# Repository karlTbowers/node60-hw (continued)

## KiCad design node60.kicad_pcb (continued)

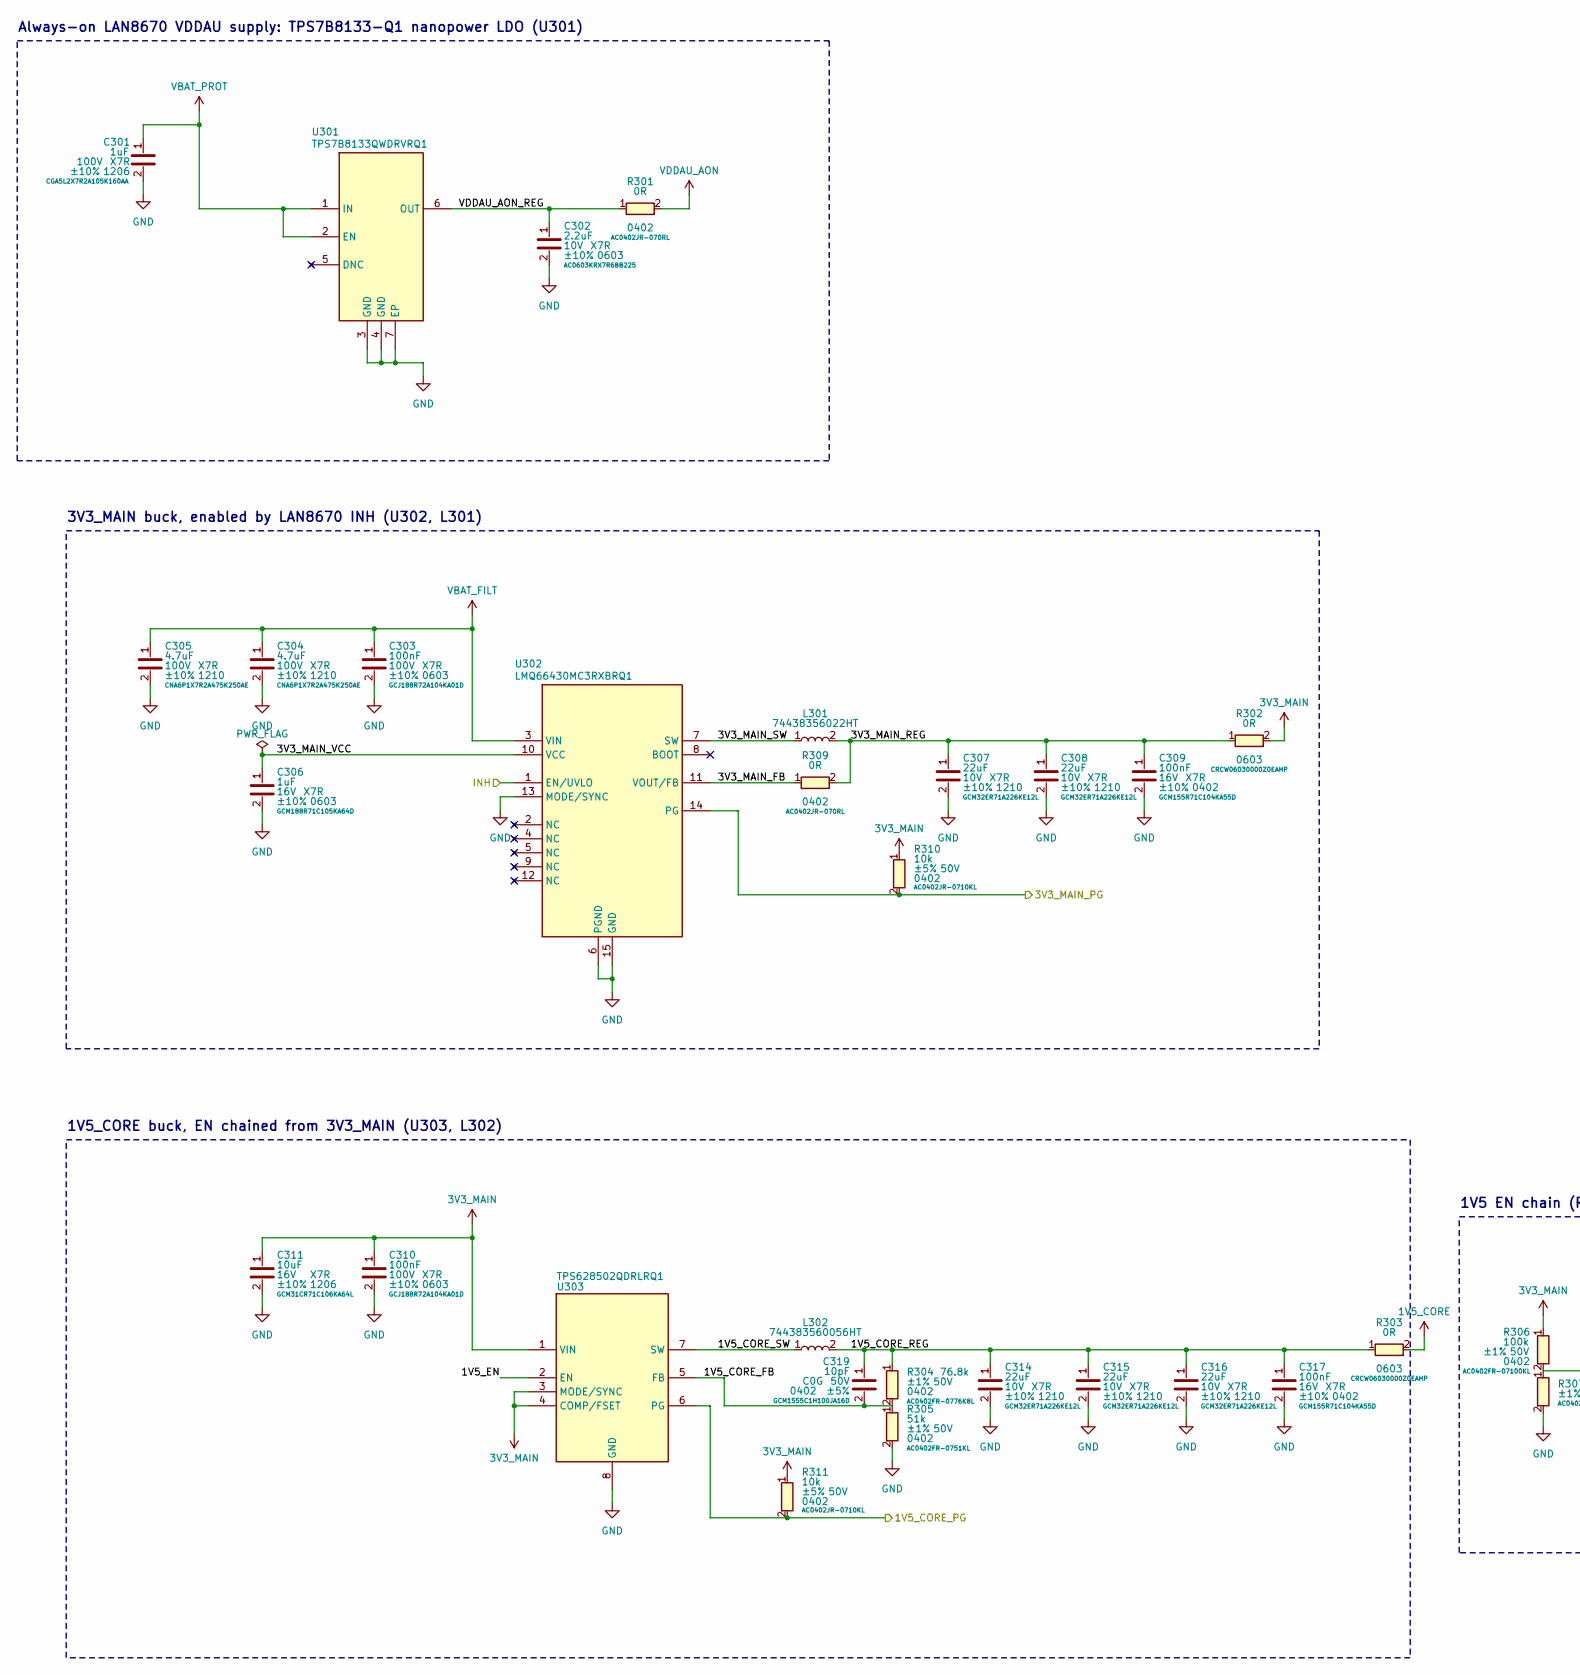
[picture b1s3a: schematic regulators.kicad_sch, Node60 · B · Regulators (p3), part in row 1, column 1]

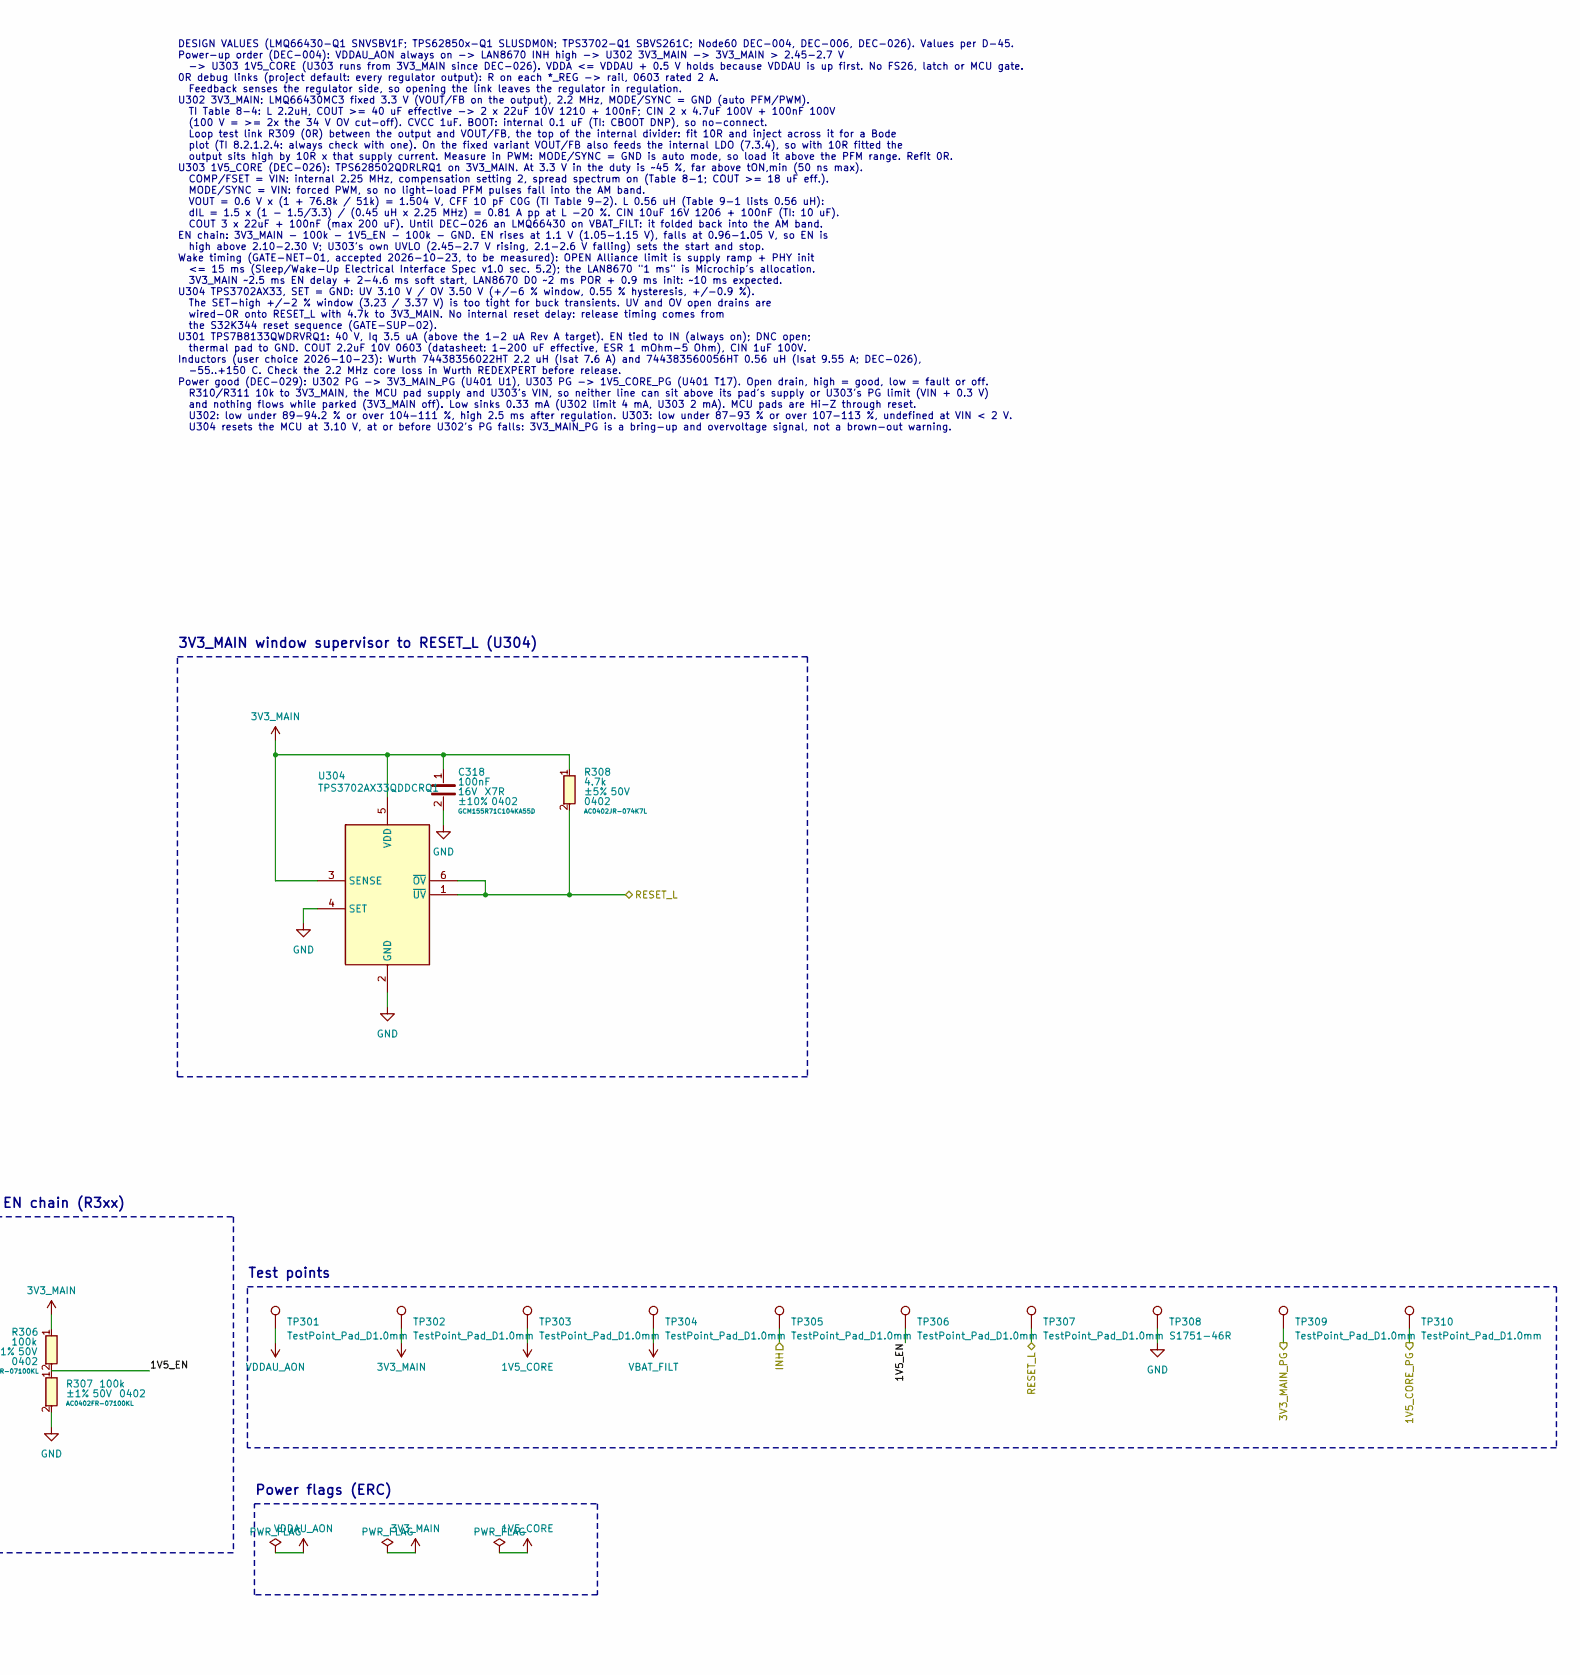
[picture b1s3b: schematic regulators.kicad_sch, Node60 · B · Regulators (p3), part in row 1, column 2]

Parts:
C301: 1uF; C_1206_3216Metric; Voltage 100V; Tolerance ±10%; MPN CGA5L2X7R2A105K160AA; DigiKey_PN 445-5845-1-ND
C302: 2.2uF; C_0603_1608Metric; Voltage 10V; Tolerance ±10%; MPN AC0603KRX7R6BB225; DigiKey_PN 13-AC0603KRX7R6BB225CT-ND
C303, C310: 100nF; C_0603_1608Metric; Voltage 100V; Tolerance ±10%; MPN GCJ188R72A104KA01D; DigiKey_PN 490-13420-1-ND
C304, C305: 4.7uF; C_1210_3225Metric; Voltage 100V; Tolerance ±10%; MPN CNA6P1X7R2A475K250AE; DigiKey_PN 445-181409-1-ND
C306: 1uF; C_0603_1608Metric; Voltage 16V; Tolerance ±10%; MPN GCM188R71C105KA64D; DigiKey_PN 490-5241-1-ND
C307, C308, C314, C315, C316: 22uF; C_1210_3225Metric; Voltage 10V; Tolerance ±10%; MPN GCM32ER71A226KE12L; DigiKey_PN 490-4797-1-ND
C309, C317, C318: 100nF; C_0402_1005Metric; Voltage 16V; Tolerance ±10%; MPN GCM155R71C104KA55D; DigiKey_PN 490-4759-1-ND
C311: 10uF; C_1206_3216Metric; Voltage 16V; Tolerance ±10%; MPN GCM31CR71C106KA64L; DigiKey_PN 490-4793-1-ND
C319: 10pF; C_0402_1005Metric; Voltage 50V; Tolerance ±5%; MPN GCM1555C1H100JA16D; DigiKey_PN 490-10668-1-ND
L301: 74438356022HT; L_Wuerth_MAPI-4020; MPN 74438356022HT; DigiKey_PN 732-74438356022HTCT-ND
L302: 744383560056HT; L_Wuerth_MAPI-4020; MPN 744383560056HT; DigiKey_PN 732-744383560056HTCT-ND
R301, R309: 0R; R_0402_1005Metric; MPN AC0402JR-070RL; DigiKey_PN 311-0.0LBCT-ND
R302, R303: 0R; R_0603_1608Metric; MPN CRCW06030000Z0EAHP; DigiKey_PN 541-0.0SBCT-ND
R304: 76.8k; R_0402_1005Metric; Tolerance ±1%; Voltage 50V; MPN AC0402FR-0776K8L; DigiKey_PN 13-AC0402FR-0776K8LCT-ND
R305: 51k; R_0402_1005Metric; Tolerance ±1%; Voltage 50V; MPN AC0402FR-0751KL; DigiKey_PN YAG3499CT-ND
R306, R307: 100k; R_0402_1005Metric; Tolerance ±1%; Voltage 50V; MPN AC0402FR-07100KL; DigiKey_PN YAG3434CT-ND
R308: 4.7k; R_0402_1005Metric; Tolerance ±5%; Voltage 50V; MPN AC0402JR-074K7L; DigiKey_PN 311-4.7KLBCT-ND
R310, R311: 10k; R_0402_1005Metric; Tolerance ±5%; Voltage 50V; MPN AC0402JR-0710KL; DigiKey_PN YAG3517CT-ND
TP301, TP302, TP303, TP304, TP305, TP306, TP307, TP309, TP310: TestPoint_Pad_D1.0mm; MPN TestPoint_Pad_D1.0mm
TP308: S1751-46R; TestPoint_Harwin_S1751; MPN S1751-46R; DigiKey_PN 952-1478-1-ND
U301: TPS7B8133QWDRVRQ1; Texas_DRV0006A_WSON-6-1EP_2x2mm_P0.65mm_EP1x1.6mm; MPN TPS7B8133QWDRVRQ1; DigiKey_PN 296-TPS7B8133QWDRVRQ1CT-ND
U302: LMQ66430MC3RXBRQ1; Texas_RXB0014A_VQFN-14-1EP_2.6x2.6mm_P0.5mm_EP1x1mm; MPN LMQ66430MC3RXBRQ1; DigiKey_PN 296-LMQ66430MC3RXBRQ1CT-ND
U303: TPS628502QDRLRQ1; Texas_DRL0008A_SOT-583-8; MPN TPS628502QDRLRQ1; DigiKey_PN 296-TPS628502QDRLRQ1CT-ND
U304: TPS3702AX33QDDCRQ1; Texas_DDC0006A_TSOT-23-6; MPN TPS3702AX33QDDCRQ1; DigiKey_PN 296-51914-2-ND

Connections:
1V5_CORE: R303.2, TP303.1 (1_1); also elsewhere on the board
3V3_MAIN: C310.1, C311.1, C318.1, R302.2, R306.1, R308.1, R310.1, R311.1, TP302.1 (1_1), U303.1 (VIN), U303.3 (MODE/SYNC), U303.4 (COMP/FSET), U304.3 (SENSE), U304.5 (VDD); also elsewhere on the board
/1V5_CORE_PG: R311.2, TP310.1 (1_1), U303.6 (PG); also elsewhere on the board
/3V3_MAIN_PG: R310.2, TP309.1 (1_1), U302.14 (PG); also elsewhere on the board
/INH: TP305.1 (1_1), U302.1 (EN/UVLO); also elsewhere on the board
/RESET_L: R308.2, TP307.1 (1_1), U304.1 (~UV), U304.6 (~OV); also elsewhere on the board
/Regulators/1V5_CORE_FB: C319.2, R304.2, R305.1, U303.5 (FB)
/Regulators/1V5_CORE_REG: C314.1, C315.1, C316.1, C317.1, C319.1, L302.2, R303.1, R304.1
/Regulators/1V5_CORE_SW: L302.1, U303.7 (SW)
/Regulators/1V5_EN: R306.2, R307.1, TP306.1 (1_1), U303.2 (EN)
/Regulators/3V3_MAIN_FB: R309.1, U302.11 (VOUT/FB)
/Regulators/3V3_MAIN_REG: C307.1, C308.1, C309.1, L301.2, R302.1, R309.2
/Regulators/3V3_MAIN_SW: L301.1, U302.7 (SW)
/Regulators/3V3_MAIN_VCC: C306.1, U302.10 (VCC)
/Regulators/VDDAU_AON_REG: C302.1, R301.1, U301.6 (OUT)
GND: C301.2, C302.2, C303.2, C304.2, C305.2, C306.2, C307.2, C308.2, C309.2, C310.2, C311.2, C314.2, C315.2, C316.2, C317.2, C318.2, R305.2, R307.2, TP308.1 (1_1), U301.3 (GND), U301.4 (GND), U301.7 (EP), U302.6 (PGND), U302.13 (MODE/SYNC), U302.15 (GND), U303.8 (GND), U304.2 (GND), U304.4 (SET); also elsewhere on the board
VBAT_FILT: C303.1, C304.1, C305.1, TP304.1 (1_1), U302.3 (VIN); also elsewhere on the board
VBAT_PROT: C301.1, U301.1 (IN), U301.2 (EN); also elsewhere on the board
VDDAU_AON: R301.2, TP301.1 (1_1); also elsewhere on the board

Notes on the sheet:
Always-on LAN8670 VDDAU supply: TPS7B8133-Q1 nanopower LDO (U301)
DESIGN VALUES (LMQ66430-Q1 SNVSBV1F; TPS62850x-Q1 SLUSDM0N; TPS3702-Q1 SBVS261C; Node60 DEC-004, DEC-006, DEC-026). Values per D-45. Power-up order (DEC-004): VDDAU_AON always on -> LAN8670 INH high -> U302 3V3_MAIN -> 3V3_MAIN > 2.45-2.7 V -> U303 1V5_CORE (U303 runs from 3V3_MAIN since DEC-026). 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
1V5_CORE buck, EN chained from 3V3_MAIN (U303, L302)
3V3_MAIN buck, enabled by LAN8670 INH (U302, L301)
Power flags (ERC)
Test points
1V5 EN chain (R3xx)
3V3_MAIN window supervisor to RESET_L (U304)

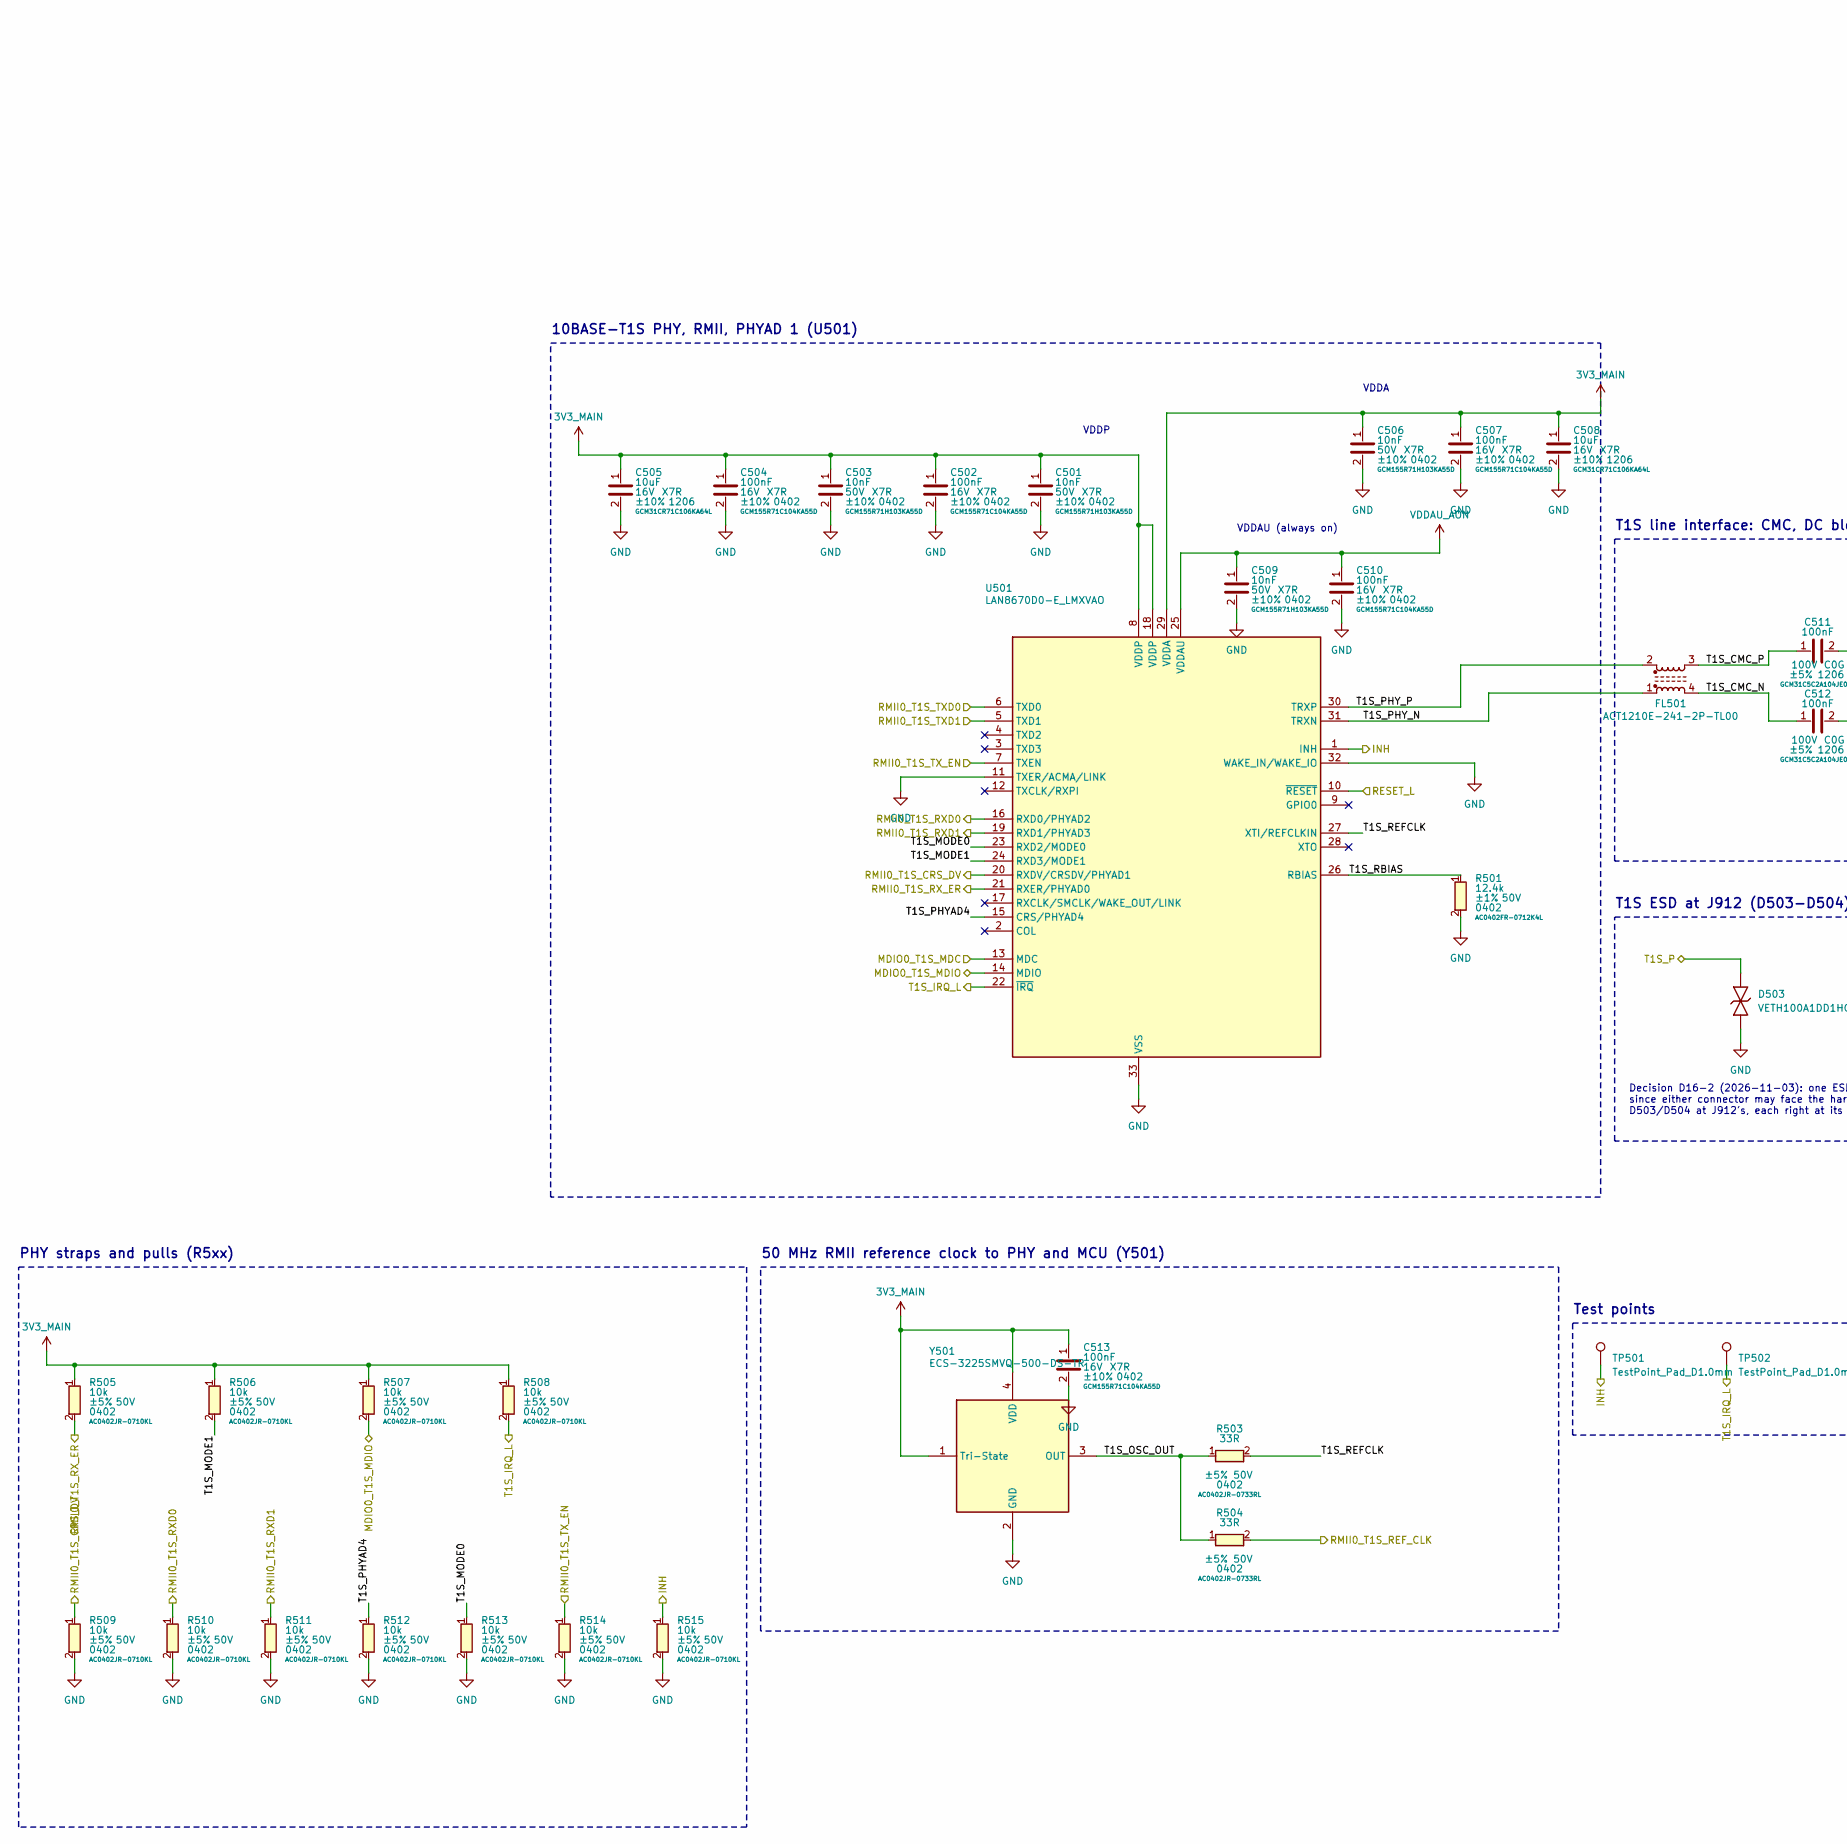
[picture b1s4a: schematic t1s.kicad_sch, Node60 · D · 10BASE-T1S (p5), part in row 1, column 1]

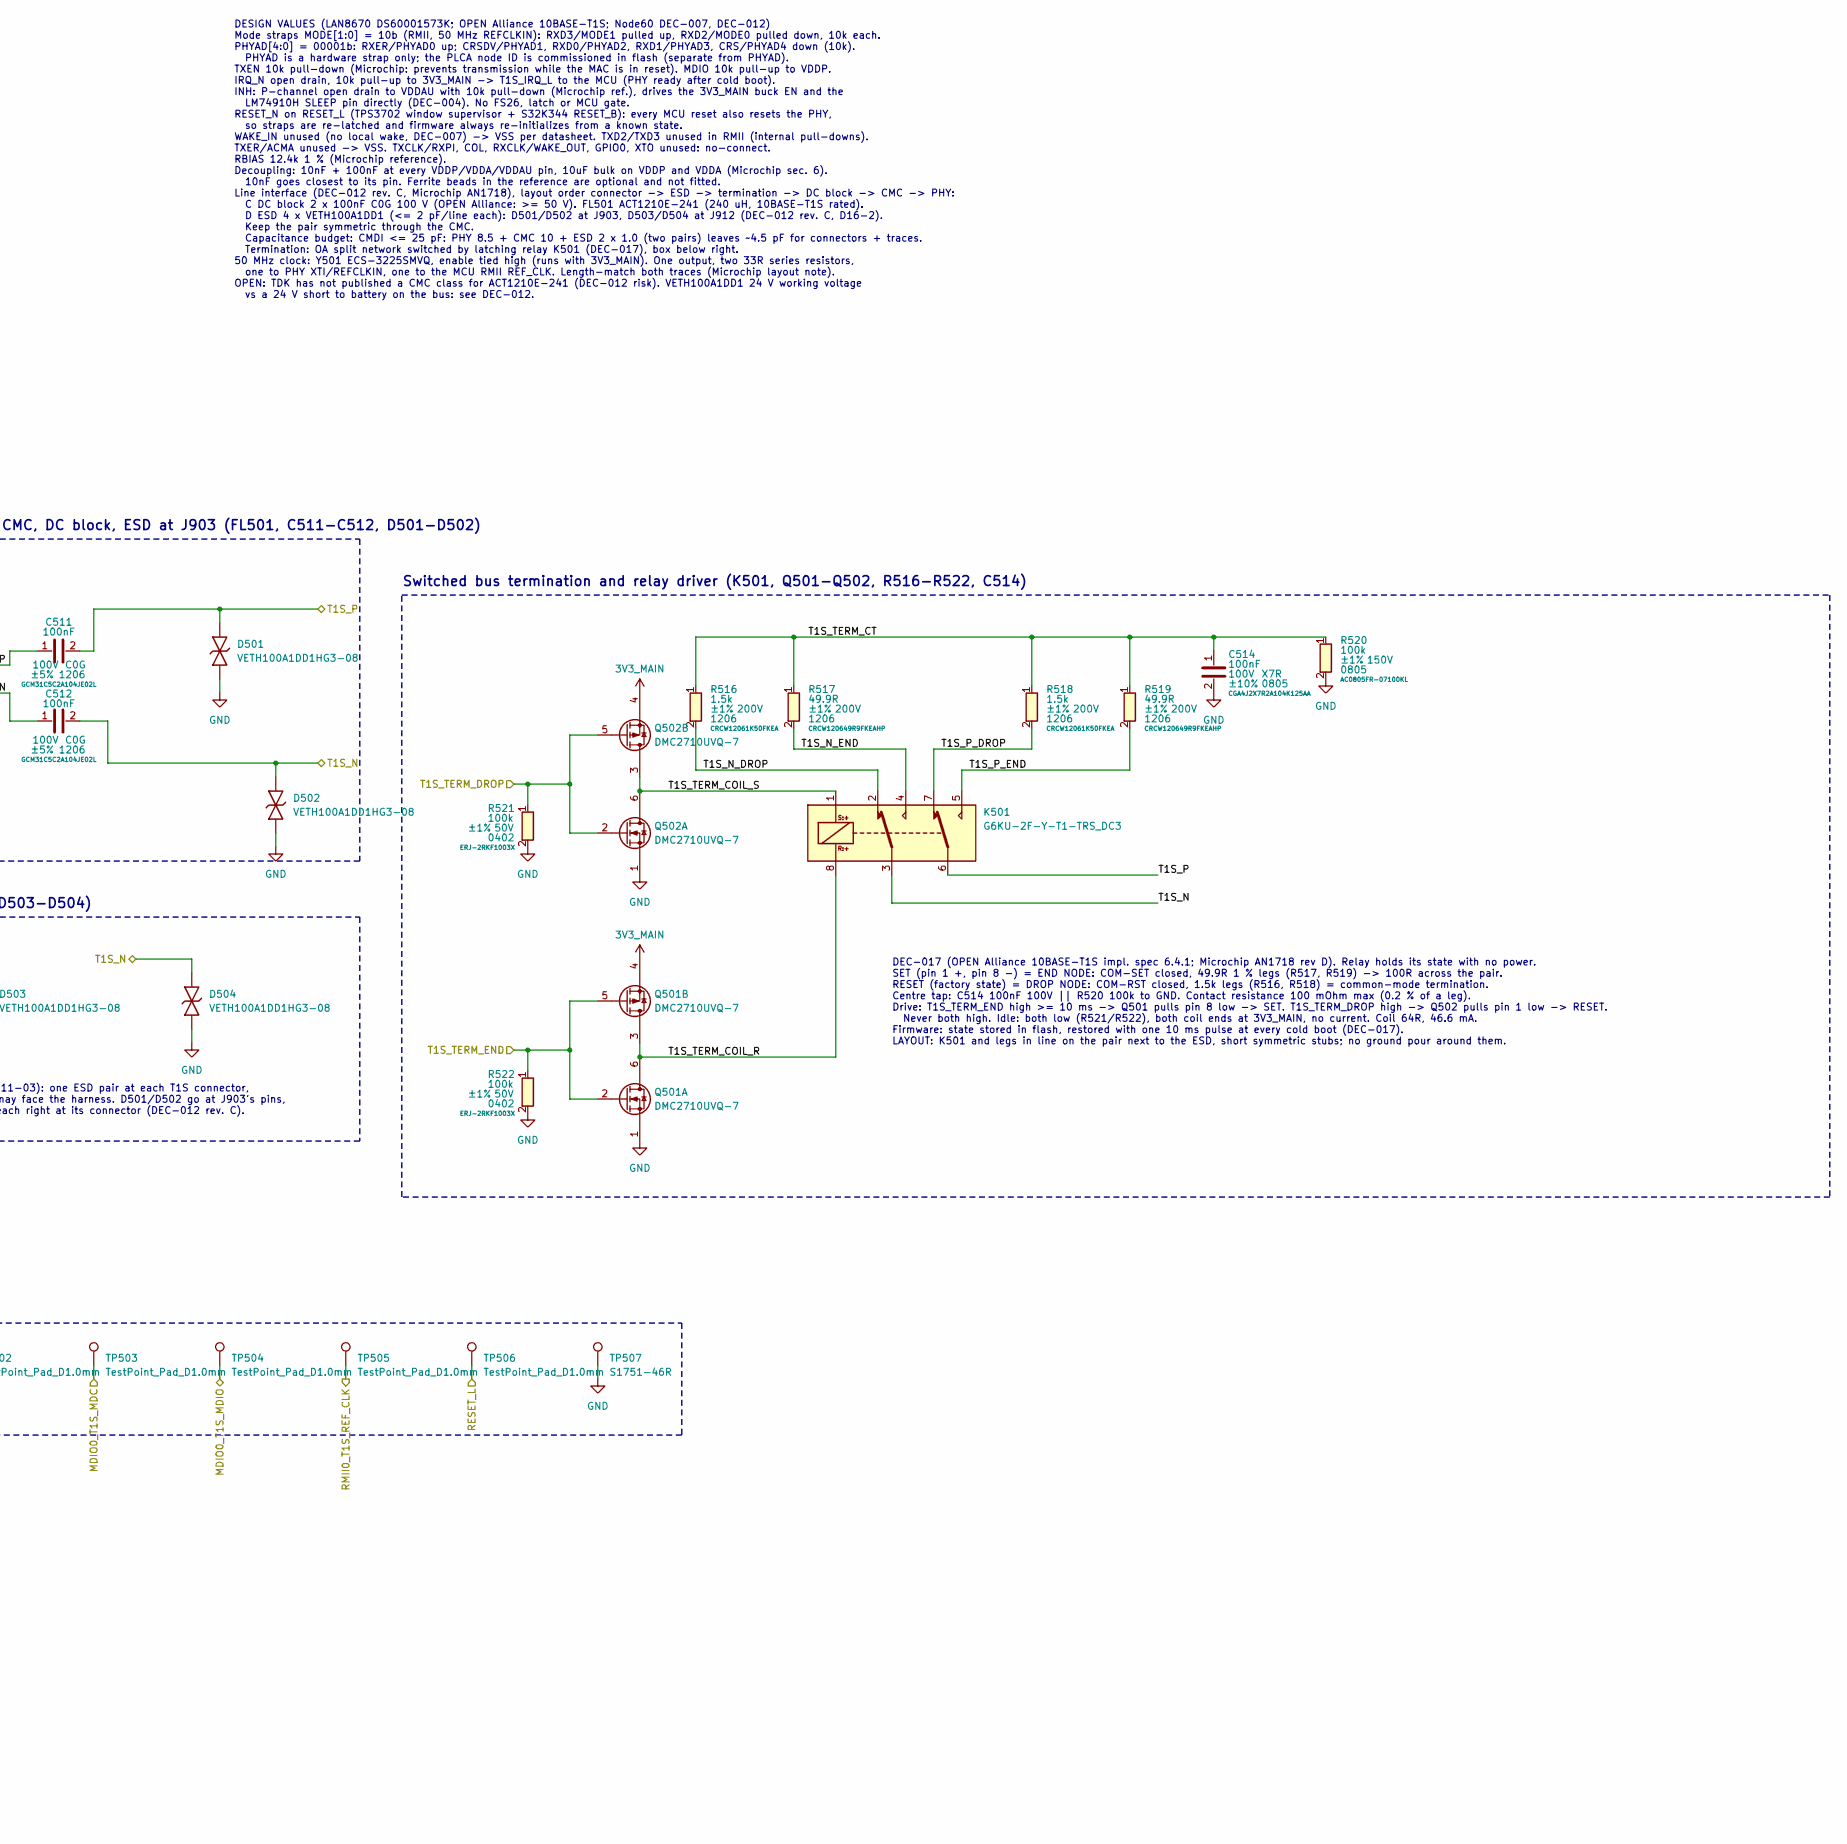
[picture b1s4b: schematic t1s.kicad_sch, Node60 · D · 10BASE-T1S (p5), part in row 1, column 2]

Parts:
C501, C503, C506, C509: 10nF; C_0402_1005Metric; Voltage 50V; Tolerance ±10%; MPN GCM155R71H103KA55D; DigiKey_PN 490-4762-1-ND
C502, C504, C507, C510, C513: 100nF; C_0402_1005Metric; Voltage 16V; Tolerance ±10%; MPN GCM155R71C104KA55D; DigiKey_PN 490-4759-1-ND
C505, C508: 10uF; C_1206_3216Metric; Voltage 16V; Tolerance ±10%; MPN GCM31CR71C106KA64L; DigiKey_PN 490-4793-1-ND
C511, C512: 100nF; C_1206_3216Metric; Voltage 100V; Tolerance ±5%; MPN GCM31C5C2A104JE02L; DigiKey_PN 490-GCM31C5C2A104JE02LCT-ND
C514: 100nF; C_0805_2012Metric; Voltage 100V; Tolerance ±10%; MPN CGA4J2X7R2A104K125AA; DigiKey_PN 445-5827-1-ND
D501, D502, D503, D504: VETH100A1DD1HG3-08; Vishay_DFN1006-2B_1.0x0.6mm; MPN VETH100A1DD1HG3-08; DigiKey_PN 112-VETH100A1DD1HG3-08CT-ND
FL501: ACT1210E-241-2P-TL00; L_CommonModeChoke_TDK_ACT1210E_3.2x2.5mm; MPN ACT1210E-241-2P-TL00; DigiKey_PN 445-ACT1210E-241-2P-TL00CT-ND
K501: G6KU-2F-Y-T1-TRS_DC3; Relay_DPDT_Omron_G6K-2F-Y; MPN G6KU-2F-Y-T1-TRS DC3; DigiKey_PN 39-G6KU-2F-Y-T1-TRSDC3TR-ND
Q501, Q502: DMC2710UVQ-7; Diodes_SOT-563; MPN DMC2710UVQ-7; DigiKey_PN 31-DMC2710UVQ-7CT-ND
R501: 12.4k; R_0402_1005Metric; Tolerance ±1%; Voltage 50V; MPN AC0402FR-0712K4L; DigiKey_PN YAG5256CT-ND
R503, R504: 33R; R_0402_1005Metric; Tolerance ±5%; Voltage 50V; MPN AC0402JR-0733RL; DigiKey_PN YAG3543CT-ND
R505, R506, R507, R508, R509, R510, R511, R512, R513, R514, R515: 10k; R_0402_1005Metric; Tolerance ±5%; Voltage 50V; MPN AC0402JR-0710KL; DigiKey_PN YAG3517CT-ND
R516, R518: 1.5k; R_1206_3216Metric; Tolerance ±1%; Voltage 200V; MPN CRCW12061K50FKEA; DigiKey_PN 541-1.50KFCT-ND
R517, R519: 49.9R; R_1206_3216Metric; Tolerance ±1%; Voltage 200V; MPN CRCW120649R9FKEAHP; DigiKey_PN 541-49.9UCT-ND
R520: 100k; R_0805_2012Metric; Tolerance ±1%; Voltage 150V; MPN AC0805FR-07100KL; DigiKey_PN YAG3688CT-ND
R521, R522: 100k; R_0402_1005Metric; Tolerance ±1%; Voltage 50V; MPN ERJ-2RKF1003X; DigiKey_PN P100KLCT-ND
TP501, TP502, TP503, TP504, TP505, TP506: TestPoint_Pad_D1.0mm; MPN TestPoint_Pad_D1.0mm
TP507: S1751-46R; TestPoint_Harwin_S1751; MPN S1751-46R; DigiKey_PN 952-1478-1-ND
U501: LAN8670D0-E_LMXVAO; Microchip_LMX_VQFN-32-1EP_5x5mm_P0.5mm_EP3.5x3.5mm; MPN LAN8670D0-E/LMXVAO
Y501: ECS-3225SMVQ-500-DS-TR; Oscillator_SMD_ECS_LGA-4_2.5x3.2mm_P2.3mm; MPN ECS-3225SMVQ-500-DS-TR; DigiKey_PN 50-ECS-3225SMVQ-500-DS-TRCT-ND

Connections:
3V3_MAIN: C501.1, C502.1, C503.1, C504.1, C505.1, C506.1, C507.1, C508.1, C513.1, Q501.4 (S2), Q502.4 (S2), R505.1, R506.1, R507.1, R508.1, U501.8 (VDDP), U501.18 (VDDP), U501.29 (VDDA), Y501.1 (Tri-State), Y501.4 (VDD); also elsewhere on the board
/INH: R515.1, TP501.1 (1_1), U501.1 (INH); also elsewhere on the board
/MDIO0_T1S_MDC: TP503.1 (1_1), U501.13 (MDC); also elsewhere on the board
/MDIO0_T1S_MDIO: R507.2, TP504.1 (1_1), U501.14 (MDIO); also elsewhere on the board
/RESET_L: TP506.1 (1_1), U501.10 (~RESET); also elsewhere on the board
/RMII0_T1S_CRS_DV: R509.1, U501.20 (RXDV/CRSDV/PHYAD1); also elsewhere on the board
/RMII0_T1S_REF_CLK: R504.2, TP505.1 (1_1); also elsewhere on the board
/RMII0_T1S_RXD0: R510.1, U501.16 (RXD0/PHYAD2); also elsewhere on the board
/RMII0_T1S_RXD1: R511.1, U501.19 (RXD1/PHYAD3); also elsewhere on the board
/RMII0_T1S_RX_ER: R505.2, U501.21 (RXER/PHYAD0); also elsewhere on the board
/RMII0_T1S_TXD0: U501.6 (TXD0); also elsewhere on the board
/RMII0_T1S_TXD1: U501.5 (TXD1); also elsewhere on the board
/RMII0_T1S_TX_EN: R514.1, U501.7 (TXEN); also elsewhere on the board
/T1S/T1S_CMC_N: C512.1, FL501.4
/T1S/T1S_CMC_P: C511.1, FL501.3
/T1S/T1S_MODE0: R513.1, U501.23 (RXD2/MODE0)
/T1S/T1S_MODE1: R506.2, U501.24 (RXD3/MODE1)
/T1S/T1S_N_DROP: K501.2 (RST1), R516.2
/T1S/T1S_N_END: K501.4 (SET1), R517.2
/T1S/T1S_OSC_OUT: R503.1, R504.1, Y501.3 (OUT)
/T1S/T1S_PHYAD4: R512.1, U501.15 (CRS/PHYAD4)
/T1S/T1S_PHY_N: FL501.1, U501.31 (TRXN)
/T1S/T1S_PHY_P: FL501.2, U501.30 (TRXP)
/T1S/T1S_P_DROP: K501.7 (RST2), R518.2
/T1S/T1S_P_END: K501.5 (SET2), R519.2
/T1S/T1S_RBIAS: R501.1, U501.26 (RBIAS)
/T1S/T1S_REFCLK: R503.2, U501.27 (XTI/REFCLKIN)
/T1S/T1S_TERM_COIL_R: K501.8 (R+), Q501.3 (D2), Q501.6 (D1)
/T1S/T1S_TERM_COIL_S: K501.1 (S+), Q502.3 (D2), Q502.6 (D1)
/T1S/T1S_TERM_CT: C514.1, R516.1, R517.1, R518.1, R519.1, R520.1
/T1S_IRQ_L: R508.2, TP502.1 (1_1), U501.22 (~IRQ); also elsewhere on the board
/T1S_N: C512.2, D502.2 (A2), D504.2 (A2), K501.3 (COM1); also elsewhere on the board
/T1S_P: C511.2, D501.2 (A2), D503.2 (A2), K501.6 (COM2); also elsewhere on the board
/T1S_TERM_DROP: Q502.2 (G1), Q502.5 (G2), R521.1; also elsewhere on the board
/T1S_TERM_END: Q501.2 (G1), Q501.5 (G2), R522.1; also elsewhere on the board
GND: C501.2, C502.2, C503.2, C504.2, C505.2, C506.2, C507.2, C508.2, C509.2, C510.2, C513.2, C514.2, D501.1 (A1), D502.1 (A1), D503.1 (A1), D504.1 (A1), Q501.1 (S1), Q502.1 (S1), R501.2, R509.2, R510.2, R511.2, R512.2, R513.2, R514.2, R515.2, R520.2, R521.2, R522.2, TP507.1 (1_1), U501.11 (TXER/ACMA/LINK), U501.32 (WAKE_IN/WAKE_IO), U501.33 (VSS), Y501.2 (GND); also elsewhere on the board
VDDAU_AON: C509.1, C510.1, U501.25 (VDDAU); also elsewhere on the board

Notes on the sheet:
VDDAU (always on)
T1S line interface: CMC, DC block, ESD at J903 (FL501, C511-C512, D501-D502)
10BASE-T1S PHY, RMII, PHYAD 1 (U501)
PHY straps and pulls (R5xx)
Test points
Decision D16-2 (2026-11-03): one ESD pair at each T1S connector, since either connector may face the harness. D501/D502 go at J903's pins, D503/D504 at J912's, each right at its connector (DEC-012 rev. C).
DEC-017 (OPEN Alliance 10BASE-T1S impl. spec 6.4.1; Microchip AN1718 rev D). Relay holds its state with no power. SET (pin 1 +, pin 8 -) = END NODE: COM-SET closed, 49.9R 1 % legs (R517, R519) -> 100R across the pair. RESET (factory state) = DROP NODE: COM-RST closed, 1.5k legs (R516, R518) = commo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
T1S ESD at J912 (D503-D504)
VDDA
50 MHz RMII reference clock to PHY and MCU (Y501)
VDDP
DESIGN VALUES (LAN8670 DS60001573K; OPEN Alliance 10BASE-T1S; Node60 DEC-007, DEC-012) Mode straps MODE[1:0] = 10b (RMII, 50 MHz REFCLKIN): RXD3/MODE1 pulled up, RXD2/MODE0 pulled down, 10k each. PHYAD[4:0] = 00001b: RXER/PHYAD0 up; CRSDV/PHYAD1, RXD0/PHYAD2, RXD1/PHYAD3, CRS/PHYAD4 down (10k). PHY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
Switched bus termination and relay driver (K501, Q501-Q502, R516-R522, C514)
